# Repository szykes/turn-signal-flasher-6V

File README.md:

# Turn signal flasher on 6 V for MZ TS 125

This is a template project for old AT90*, ATmega*, and ATtiny* projects. It uses a simple testing and mocking framework and relies on own `avr-libc` version.

## Building firmware
```
cmake -S . -B cmake
```

```
cmake --build cmake --target app
```

## Building and running test
```
cmake -DTEST=True -S . -B cmake-test
```

```
cmake --build cmake-test --target app-test
```

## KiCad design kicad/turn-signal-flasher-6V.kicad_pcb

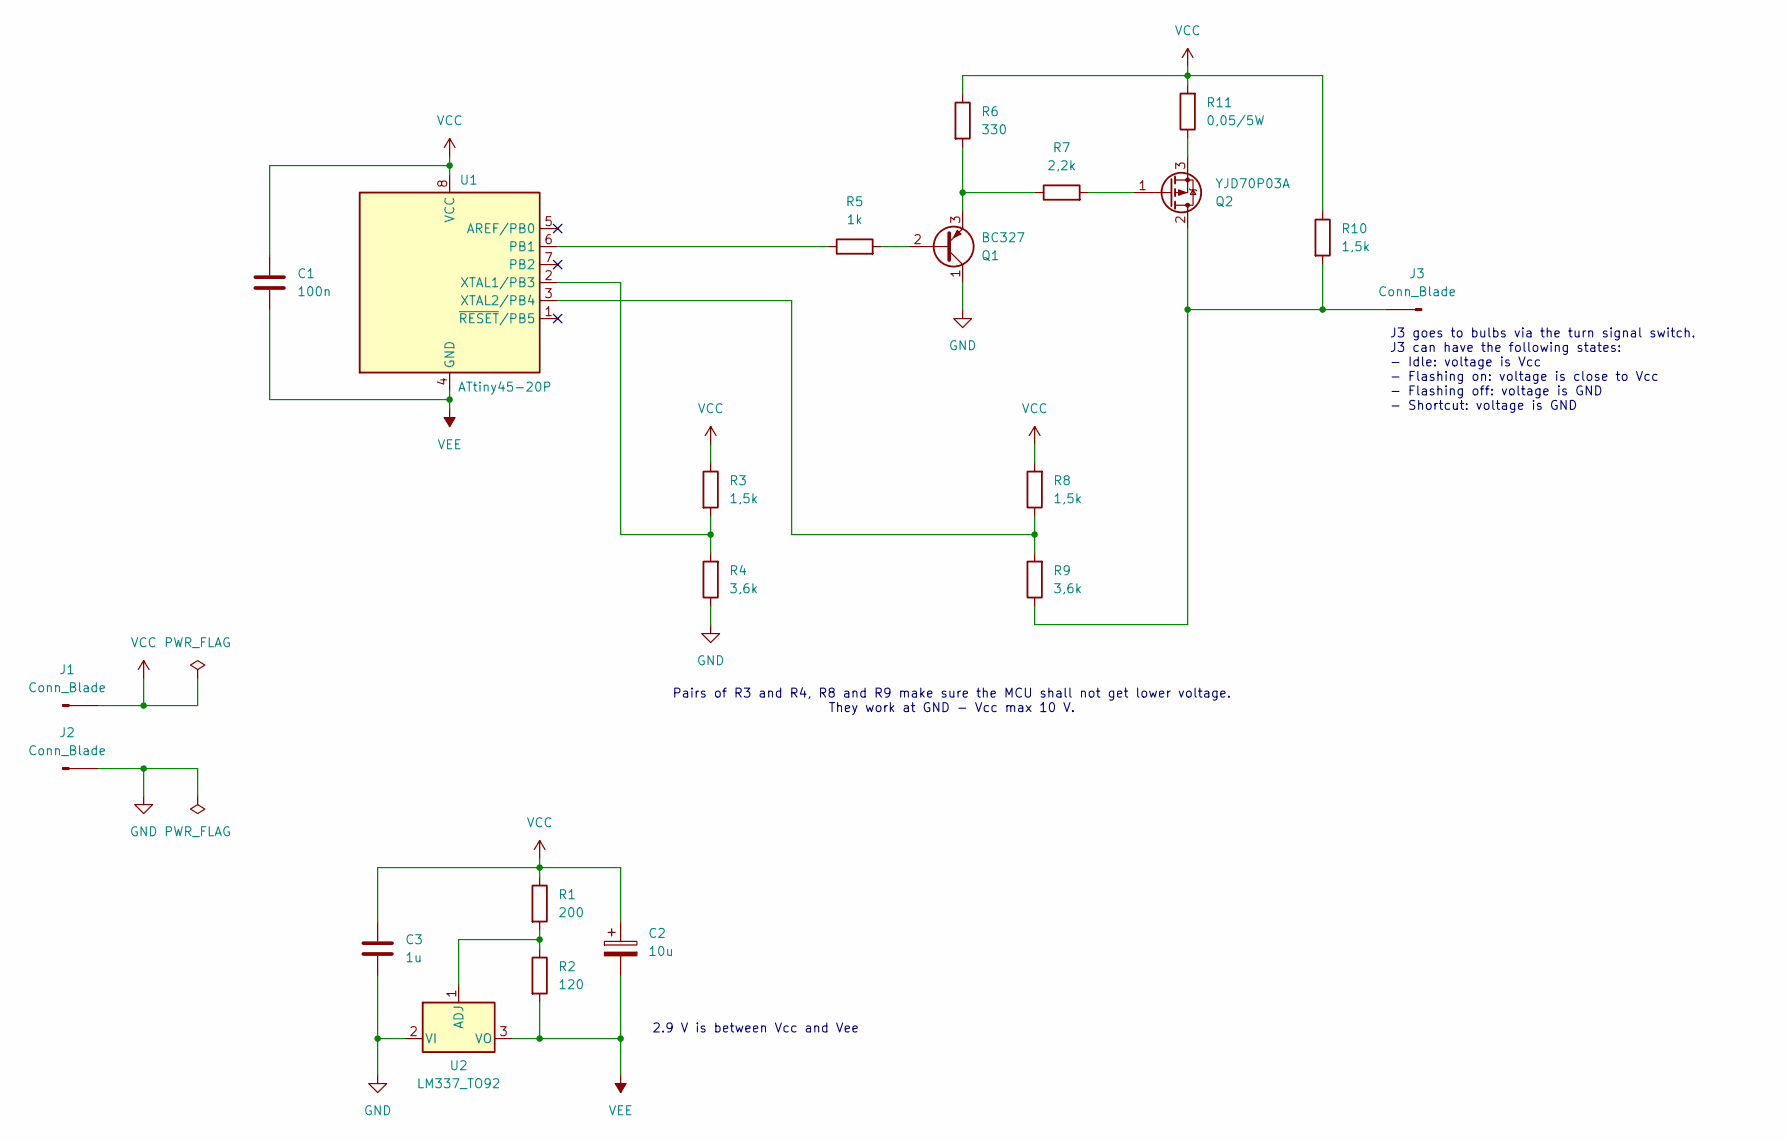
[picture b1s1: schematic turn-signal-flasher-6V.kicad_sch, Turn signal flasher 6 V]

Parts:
C1: 100n; C_1206_3216Metric_Pad1.33x1.80mm_HandSolder
C2: 10u; CP_Radial_D5.0mm_P2.00mm
C3: 1u; C_1206_3216Metric_Pad1.33x1.80mm_HandSolder
J1, J2, J3: Conn_Blade; BladeConn_6.3x0.8mm_Horizontal
Q1: BC327; TO-92_Inline
Q2: YJD70P03A; TO-252-2
R1: 200; R_1206_3216Metric_Pad1.30x1.75mm_HandSolder
R2: 120; R_1206_3216Metric_Pad1.30x1.75mm_HandSolder
R3, R8, R10: 1,5k; R_1206_3216Metric_Pad1.30x1.75mm_HandSolder
R4, R9: 3,6k; R_1206_3216Metric_Pad1.30x1.75mm_HandSolder
R5: 1k; R_1206_3216Metric_Pad1.30x1.75mm_HandSolder
R6: 330; R_1206_3216Metric_Pad1.30x1.75mm_HandSolder
R7: 2,2k; R_1206_3216Metric_Pad1.30x1.75mm_HandSolder
R11: 0,05/5W; R_Axial_DIN0617_L17.0mm_D6.0mm_P20.32mm_Horizontal
U1: ATtiny45-20P; DIP-8_W7.62mm
U2: LM337_TO92; TO-92

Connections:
GND: C3.2, J2.1, Q1.1 (C), R4.1, U2.2 (VI)
unnamed: J3.1, Q2.2 (D), R9.1, R10.2
unnamed: Q1.2 (B), R5.2
unnamed: Q1.3 (E), R6.2, R7.1
unnamed: Q2.1 (G), R7.2
unnamed: Q2.3 (S), R11.1
unnamed: R5.1, U1.6 (PB1)
unnamed: R3.2, R4.2, U1.2 (XTAL1/PB3)
unnamed: R8.1, R9.2, U1.3 (XTAL2/PB4)
unnamed: R1.2, R2.1, U2.1 (ADJ)
VCC: C1.1, C2.1, C3.1, J1.1, R1.1, R3.1, R6.1, R8.2, R10.1, R11.2, U1.8 (VCC)
VEE: C1.2, C2.2, R2.2, U1.4 (GND), U2.3 (VO)

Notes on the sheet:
Pairs of R3 and R4, R8 and R9 make sure the MCU shall not get lower voltage. They work at GND - Vcc max 10 V.
2.9 V is between Vcc and Vee
J3 goes to bulbs via the turn signal switch. J3 can have the following states: - Idle: voltage is Vcc - Flashing on: voltage is close to Vcc - Flashing off: voltage is GND - Shortcut: voltage is GND

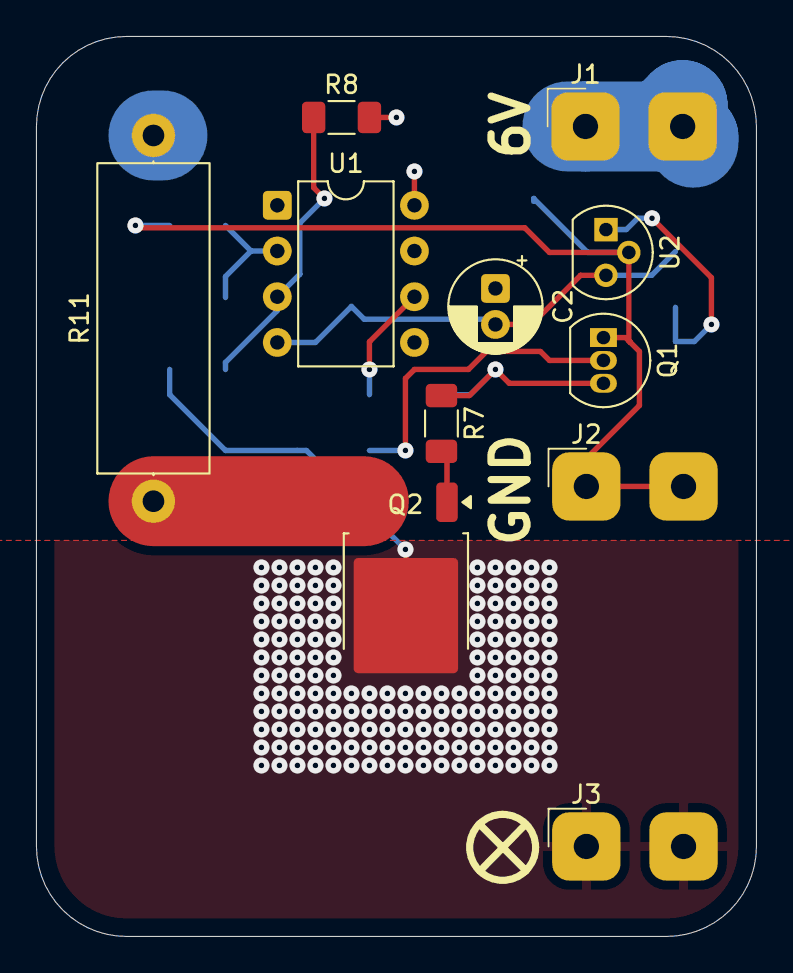
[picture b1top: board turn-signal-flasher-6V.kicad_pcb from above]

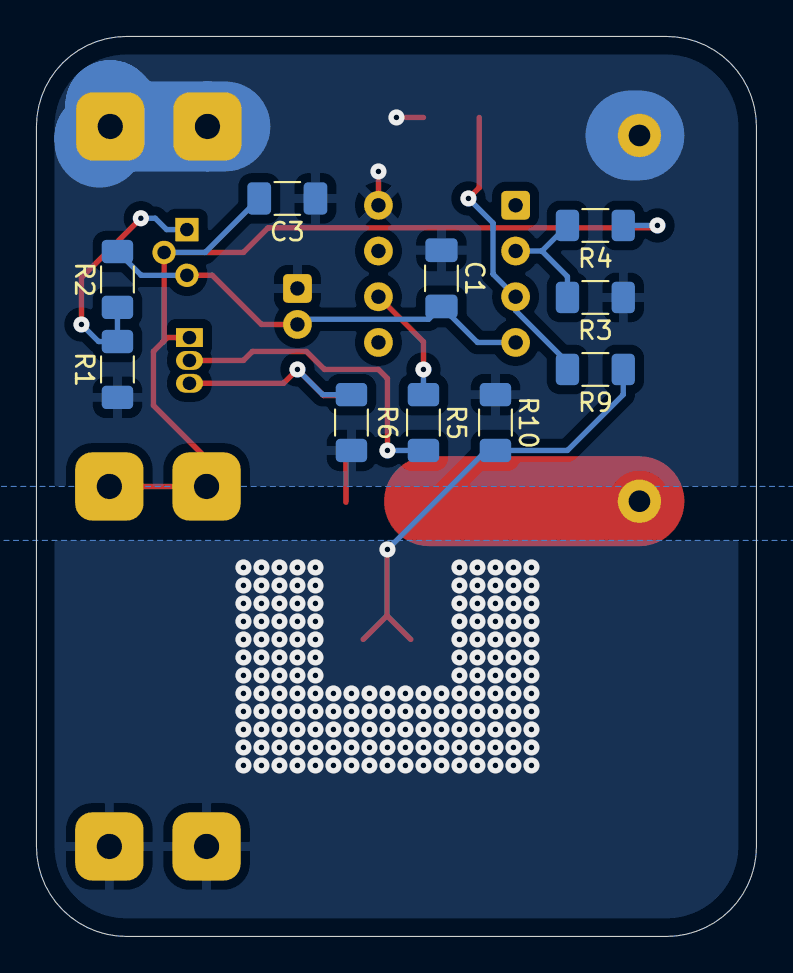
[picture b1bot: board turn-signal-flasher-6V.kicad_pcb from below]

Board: 2 copper layers, 40.0 x 50.0 mm, 21 parts (10 on the bottom side), 12 nets.

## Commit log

2025-05-12 cleaning up stuff
2025-05-12 started to write logic
2025-06-19 add kicad-lib submodule
2025-06-22 add init kicad project
2025-06-27 add init FW
2025-06-27 use avr-libc-2_2_1-release
2025-06-28 update gitignore
2025-06-28 add clang support
2025-06-28 add first TC
2025-06-28 covers app with TCs
2025-07-24 finalize PCB and code
2025-12-18 fix: cmake policy
2025-12-19 fix: overshoot of MOSFET
2025-12-19 fix: first cycle is long, wait before ADC
2025-12-20 chore: update schematic svg
2025-12-20 doc: add time period as comment
